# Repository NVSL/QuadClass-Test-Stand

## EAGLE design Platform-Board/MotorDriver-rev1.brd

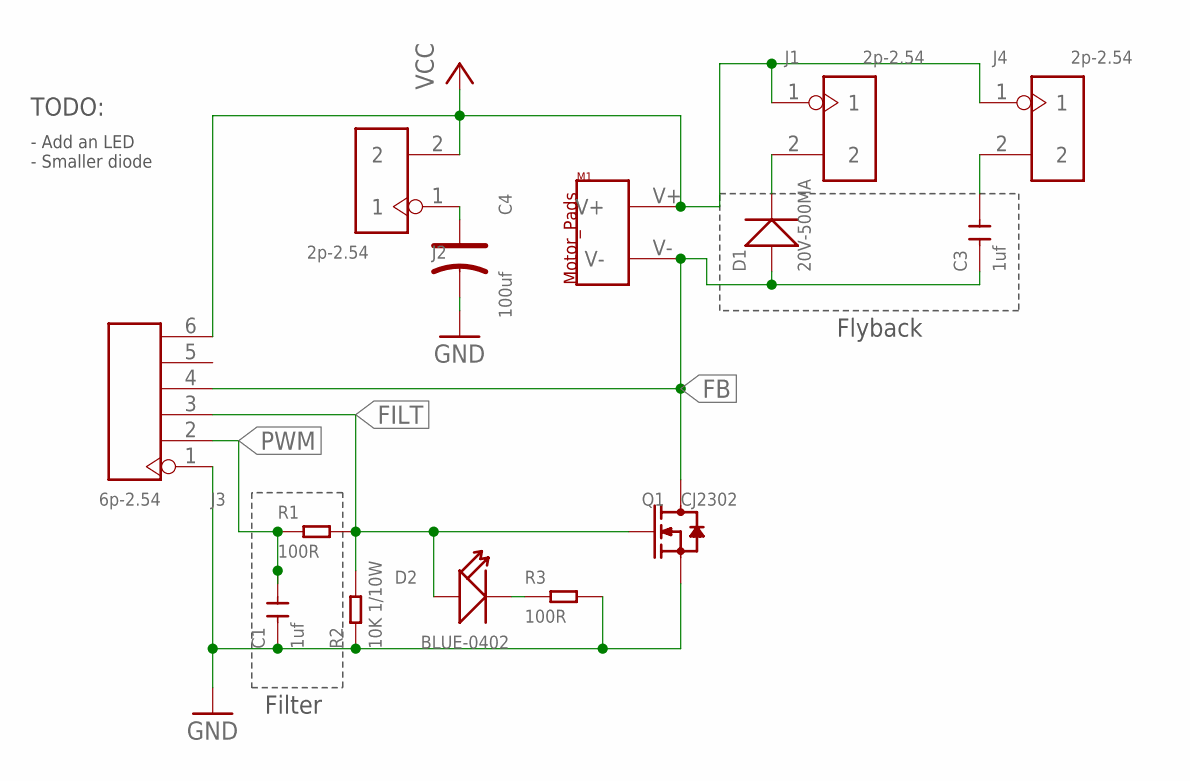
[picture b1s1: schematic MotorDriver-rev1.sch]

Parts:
C1: 1uf; C0402
C3: 1uf; C0603
C4: 100uf; AVX-B
D1: 20V-500MA; SOD-123
D2: BLUE-0402; LED-0402
J1, J2, J4: 2p-2.54; H2-2.54
J3: 6p-2.54; H6-2.54
M1: MOTOR_PADS
Q1: CJ2302; SOT-23
R1: 100R; R0603
R2: 10K 1/10W; R0603
R3: 100R; R0402

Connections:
FB: C3.1, D1.+, J3.4, M1.V-, Q1.3 (D)
FILT: D2.+, J3.3, Q1.1 (G), R1.2, R2.2
GND: C1.1, C4.-, J3.1, Q1.2 (S), R2.1, R3.2
unnamed: D2.-, R3.1
unnamed: C4.+, J2.1
unnamed: D1.-, J1.2
unnamed: C3.2, J4.2
PWM: C1.2, J3.2, R1.1
VCC: J1.1, J2.2, J3.6, J4.1, M1.V+

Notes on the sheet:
TODO:
- Add an LED - Smaller diode
Filter
Flyback

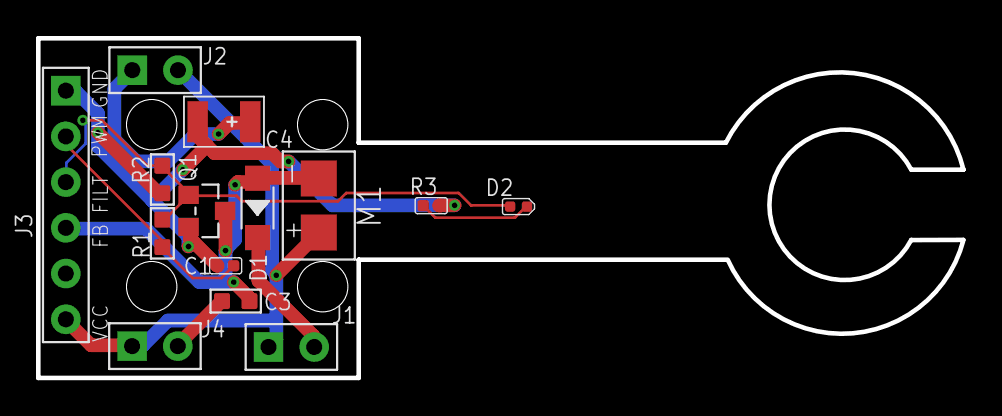
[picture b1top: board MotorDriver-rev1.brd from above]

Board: 2 copper layers, 51.4 x 18.9 mm, 14 parts (0 on the bottom side), 9 nets.

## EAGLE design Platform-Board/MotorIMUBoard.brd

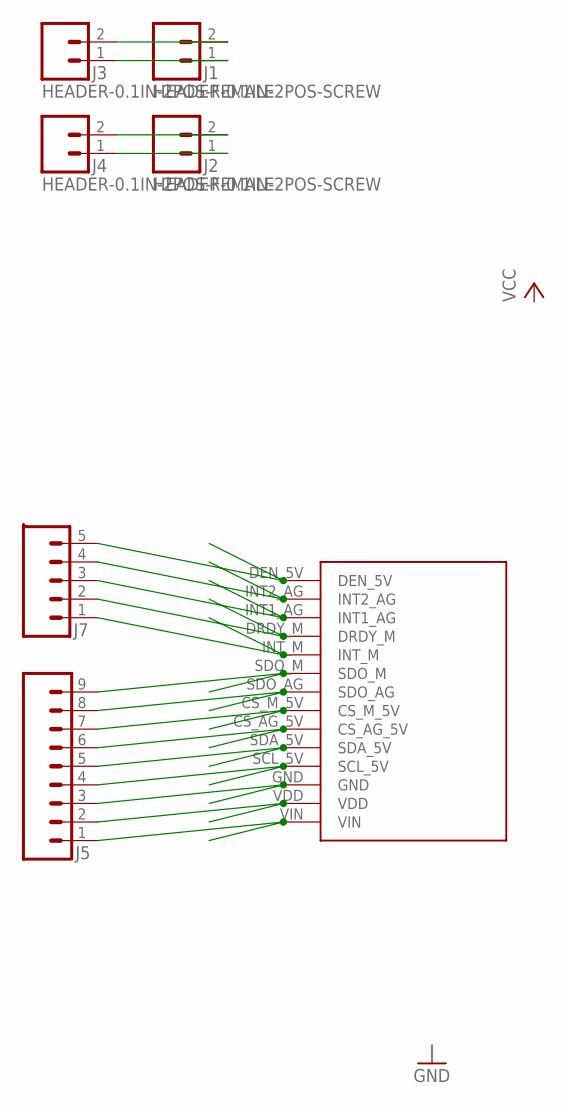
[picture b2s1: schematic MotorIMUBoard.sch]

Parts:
J1, J2: HEADER-0.1IN-2POS-SCREW; SCREW-TERMINAL-1X2-2.54MM
J3, J4: HEADER-0.1IN-2POS-FEMALE; HDRV2W63P254_2X1_508X254H838_HS
J5: HEADER-0.1IN-9POS-FEMALE; HDRV9W63P254_9X1_2286X254H838_HS
J7: HEADER-0.1IN-5POS-FEMALE; HDRV5W63P254_5X1_1270X254H838_HS
U$1: ADAFRUIT-LSM9DS1-BOB; ADAFRUIT-LSM9DS1

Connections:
unnamed: J2.1, J4.1
unnamed: J2.2, J4.2
unnamed: J1.1, J3.1
unnamed: J1.2, J3.2
unnamed: J5.1, U$1.VIN
unnamed: J5.2, U$1.VDD
unnamed: J5.3, U$1.GND
unnamed: J5.4, U$1.SCL_5V
unnamed: J5.5, U$1.SDA_5V
unnamed: J5.6, U$1.CS_AG_5V
unnamed: J5.7, U$1.CS_M_5V
unnamed: J5.8, U$1.SDO_AG
unnamed: J5.9, U$1.SDO_M
unnamed: J7.1, U$1.INT_M
unnamed: J7.2, U$1.DRDY_M
unnamed: J7.3, U$1.INT1_AG
unnamed: J7.4, U$1.INT2_AG
unnamed: J7.5, U$1.DEN_5V

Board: 2 copper layers, 7 parts (0 on the bottom side), 18 nets, no tracks yet.

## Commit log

2017-03-19 give it its own repo
2017-03-19 motor driver board to test stand
2017-03-20 Make brace into platform for devboard
2017-03-22 Higher pivot. Space for bread board. Four motors.
2017-03-23 new platform. 2 kits, one board
2017-03-23 tweaks for perma proto board
2017-03-26 tweaks
2017-03-26 Fritzing sketches for design
2018-04-28 servo mount
2018-05-19 10in test stand design
2018-05-26 code for large and small test stands
2018-05-26 more generality
2018-06-20 new stand in solid python w/ no fasteners
2018-06-20 Makefile support for solid python
2018-06-20 Tweak friction test. output all the parts for the new teststand. Remove end braces. Shrink big braces.
2019-01-21 bigger hole and unsecuretd hole
2019-02-14 platform for FCB
2019-02-14 New locking mechanism
2019-02-16 fix size pivot hole size. Add zip ties to hold platform to pivot. Increase board size. Thicker edge.
2019-02-16 thin lip to fit battery underboard
2019-03-16 Add mount for ftdi
2019-03-16 test pattern to verify that we can cut all the way across a 12x24 board
2019-05-28 stronger platform
2020-02-13 plywood airframe and board mount
2020-03-29 fix orientation of holes on platform/board mount. and top and bottom docking to side panel
2021-12-31 shrink hole in airframe since no one use the bottom-entry header holes
